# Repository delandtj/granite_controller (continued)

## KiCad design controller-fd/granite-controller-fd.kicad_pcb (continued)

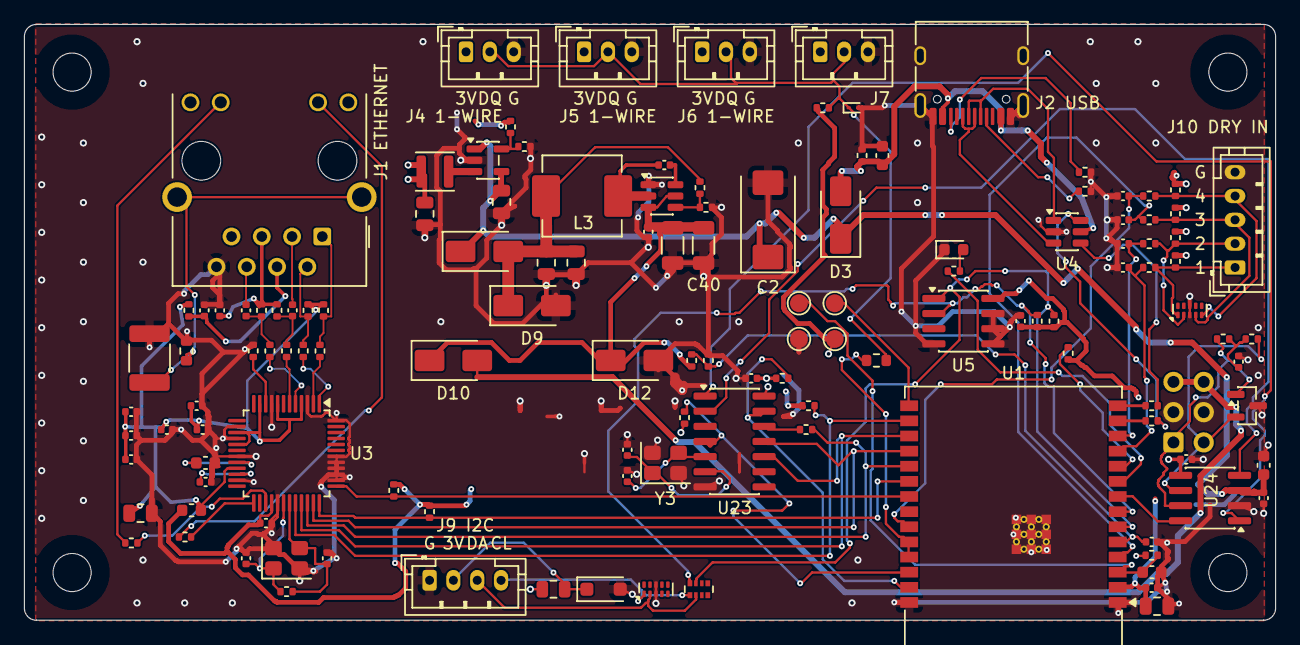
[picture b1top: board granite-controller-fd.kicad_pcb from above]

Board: 4 copper layers, 105.0 x 50.0 mm, 134 parts (1 on the bottom side), 81 nets.

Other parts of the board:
H1, H2, H3, H4: MountingHole_3.2mm_M3

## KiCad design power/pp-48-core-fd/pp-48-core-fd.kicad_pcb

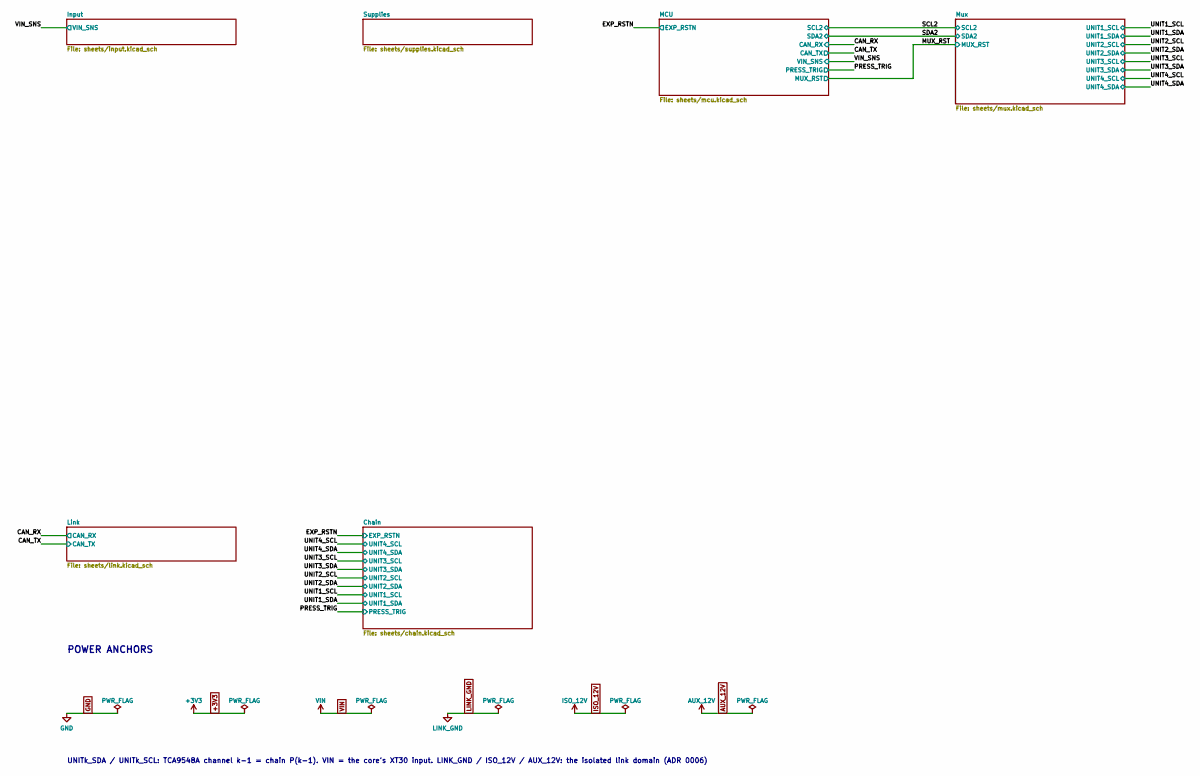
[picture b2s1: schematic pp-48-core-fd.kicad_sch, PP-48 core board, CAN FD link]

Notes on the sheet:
POWER ANCHORS
UNITk_SDA / UNITk_SCL: TCA9548A channel k-1 = chain P(k-1). VIN = the core's XT30 input. LINK_GND / ISO_12V / AUX_12V: the isolated link domain (ADR 0006)

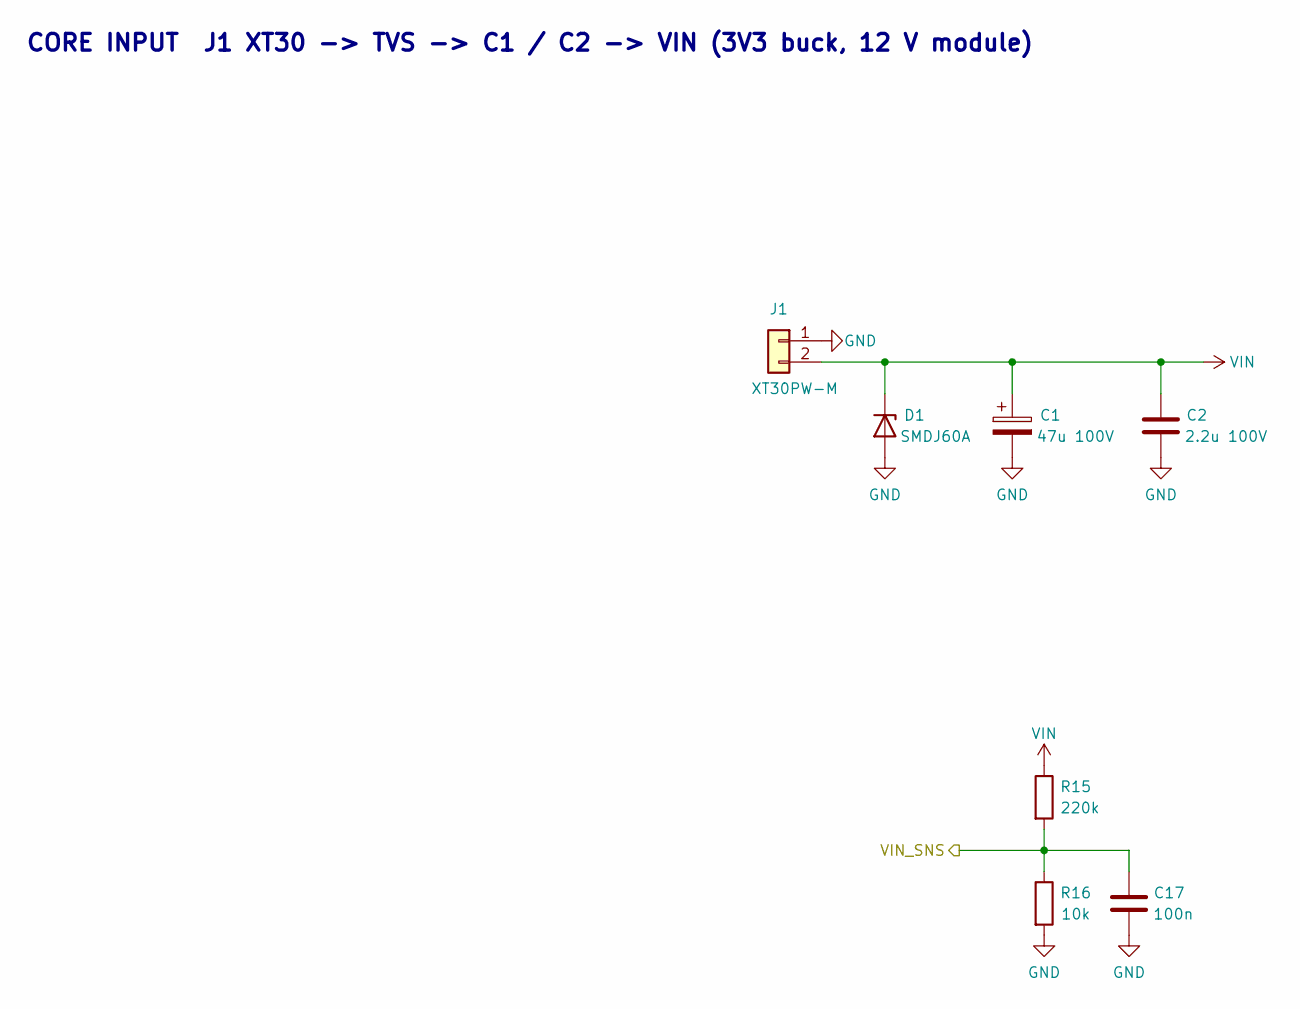
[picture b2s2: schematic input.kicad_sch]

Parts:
C1: 47u 100V; CP_Elec_10x10; MPN Lelon RVT2A470M1010; LCSC C87862
C2: 2.2u 100V; C_1210_3225Metric; LCSC C338133
C17: 100n; C_0402_1005Metric; LCSC C1525
D1: SMDJ60A; D_SMC; LCSC C2990209
J1: XT30PW-M; AMASS_XT30PW-M_1x02_P2.50mm_Horizontal; MPN Amass XT30PW-M; LCSC C431092
R15: 220k; R_0805_2012Metric; LCSC C17556
R16: 10k; R_0402_1005Metric; LCSC C25744

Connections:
/VIN_SNS: C17.1, R15.2, R16.1; also elsewhere on the board
GND: C1.2, C2.2, C17.2, D1.2 (A), J1.1, R16.2; also elsewhere on the board
VIN: C1.1, C2.1, D1.1 (K), J1.2, R15.1; also elsewhere on the board

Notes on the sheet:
CORE INPUT J1 XT30 -> TVS -> C1 / C2 -> VIN (3V3 buck, 12 V module)

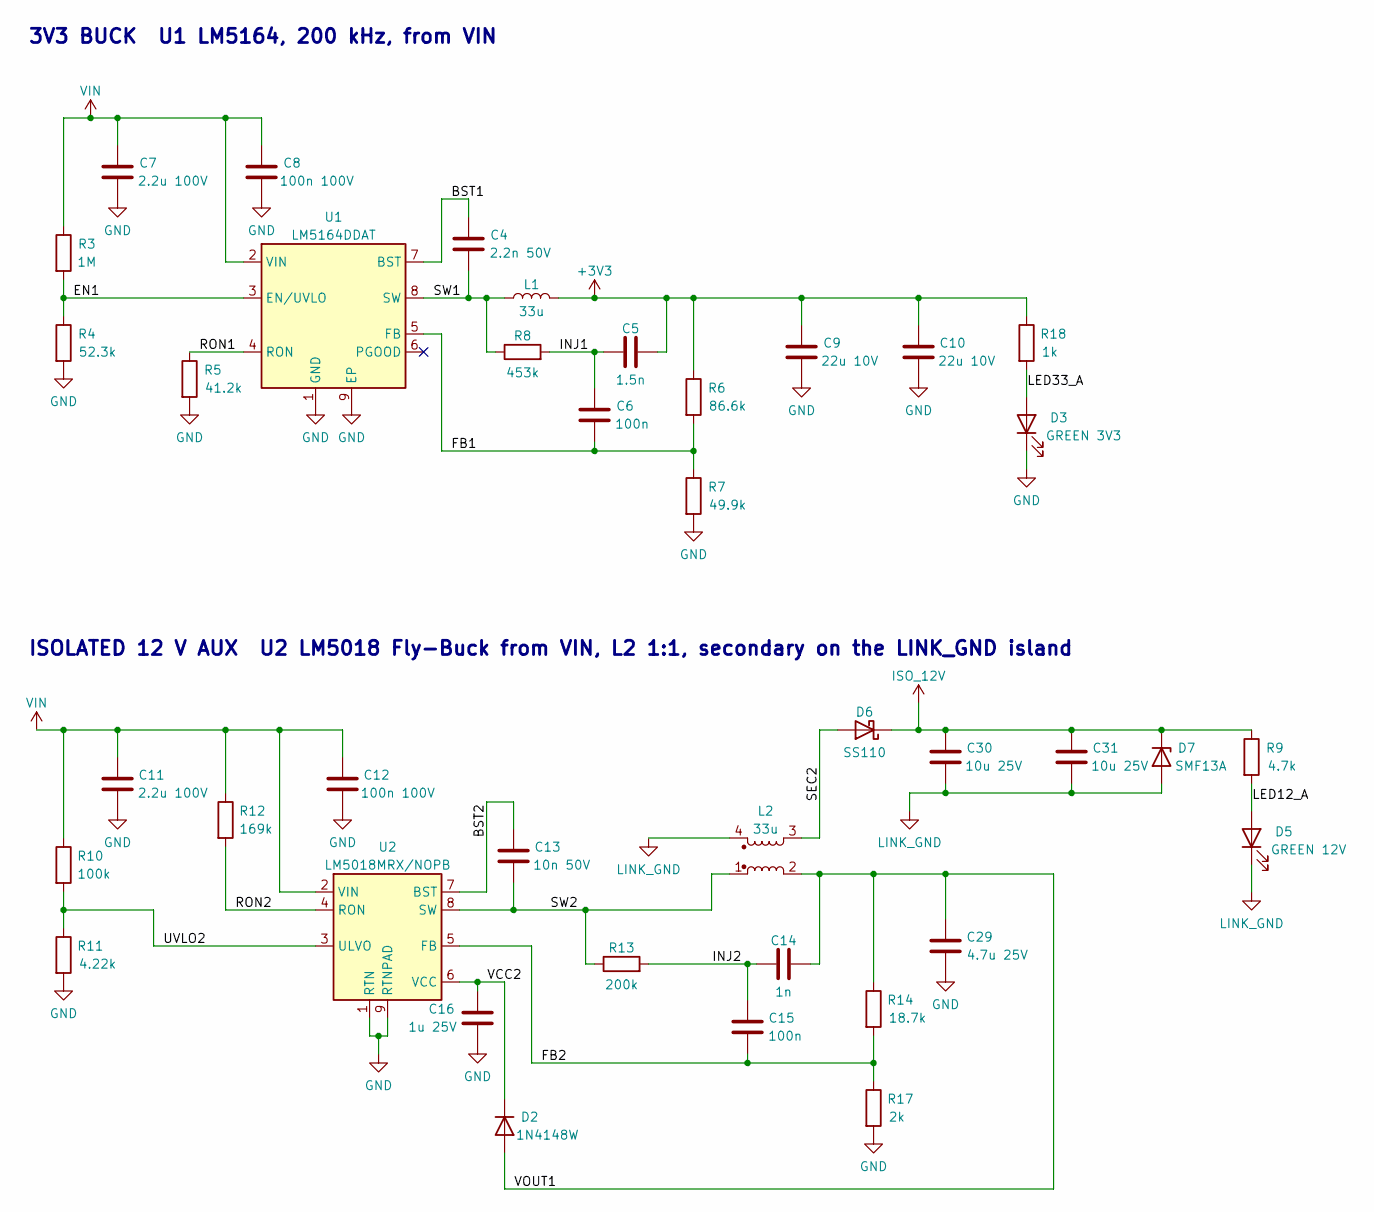
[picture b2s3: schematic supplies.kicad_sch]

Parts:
C4: 2.2n 50V; C_0402_1005Metric; LCSC C1531
C5: 1.5n; C_0402_1005Metric; LCSC C107022
C6, C15: 100n; C_0402_1005Metric; LCSC C1525
C7, C11: 2.2u 100V; C_1210_3225Metric; LCSC C338133
C8, C12: 100n 100V; C_0603_1608Metric; LCSC C696916
C9, C10: 22u 10V; C_1210_3225Metric; LCSC C318780
C13: 10n 50V; C_0402_1005Metric; LCSC C15195
C14: 1n; C_0402_1005Metric; LCSC C1523
C16: 1u 25V; C_0603_1608Metric; LCSC C15849
C29: 4.7u 25V; C_0805_2012Metric; LCSC C1779
C30, C31: 10u 25V; C_0805_2012Metric; LCSC C15850
D2: 1N4148W; D_SOD-123; LCSC C917030
D3: GREEN 3V3; LED_0603_1608Metric; LCSC C12624
D5: GREEN 12V; LED_0603_1608Metric; LCSC C12624
D6: SS110; D_SMA; LCSC C2482
D7: SMF13A; D_SOD-123F; LCSC C353315
L1: 33u; L_Bourns_SRR1260; MPN Bourns SRR1260-330M; LCSC C840528
L2: 33u; L_Coilcraft_LPD5030V; MPN Coilcraft LPD5030V-333MRC; LCSC C5441621
R3: 1M; R_0805_2012Metric; LCSC C17514
R4: 52.3k; R_0402_1005Metric; LCSC C2998086
R5: 41.2k; R_0402_1005Metric; LCSC C2998053
R6: 86.6k; R_0402_1005Metric; LCSC C48533697
R7: 49.9k; R_0402_1005Metric; LCSC C137969
R8: 453k; R_0402_1005Metric; LCSC C27009
R9: 4.7k; R_0603_1608Metric; LCSC C23162
R10: 100k; R_0805_2012Metric; LCSC C149504
R11: 4.22k; R_0402_1005Metric; LCSC C25898
R12: 169k; R_0805_2012Metric; LCSC C2933337
R13: 200k; R_0805_2012Metric; LCSC C17539
R14: 18.7k; R_0402_1005Metric; LCSC C5153953
R17: 2k; R_0402_1005Metric; LCSC C4109
R18: 1k; R_0402_1005Metric; LCSC C11702
U1: LM5164DDAT; HSOP-8-1EP_3.9x4.9mm_P1.27mm_EP2.41x3.1mm; LCSC C2071198
U2: LM5018MRX/NOPB; SOIC-8-1EP_3.9x4.9mm_P1.27mm_EP2.95x4.9mm_Mask2.71x3.4mm_Th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; LCSC C471040

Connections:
+3V3: C5.2, C9.1, C10.1, L1.2, R6.1, R18.1; also elsewhere on the board
/Supplies/BST1: C4.1, U1.7 (BST)
/Supplies/BST2: C13.1, U2.7 (BST)
/Supplies/EN1: R3.2, R4.1, U1.3 (EN/UVLO)
/Supplies/FB1: C6.2, R6.2, R7.1, U1.5 (FB)
/Supplies/FB2: C15.2, R14.2, R17.1, U2.5 (FB)
/Supplies/INJ1: C5.1, C6.1, R8.2
/Supplies/INJ2: C14.1, C15.1, R13.2
/Supplies/LED12_A: D5.2 (A), R9.2
/Supplies/LED33_A: D3.2 (A), R18.2
/Supplies/RON1: R5.1, U1.4 (RON)
/Supplies/RON2: R12.2, U2.4 (RON)
/Supplies/SEC2: D6.2 (A), L2.3
/Supplies/SW1: C4.2, L1.1, R8.1, U1.8 (SW)
/Supplies/SW2: C13.2, L2.1, R13.1, U2.8 (SW)
/Supplies/UVLO2: R10.2, R11.1, U2.3 (ULVO)
/Supplies/VCC2: C16.1, D2.1 (K), U2.6 (VCC)
/Supplies/VOUT1: C14.2, C29.1, D2.2 (A), L2.2, R14.1
GND: C7.2, C8.2, C9.2, C10.2, C11.2, C12.2, C16.2, C29.2, D3.1 (K), R4.2, R5.2, R7.2, R11.2, R17.2, U1.1 (GND), U1.9 (EP), U2.1 (RTN), U2.9 (RTNPAD); also elsewhere on the board
ISO_12V: C30.1, C31.1, D6.1 (K), D7.1 (K), R9.1; also elsewhere on the board
LINK_GND: C30.2, C31.2, D5.1 (K), D7.2 (A), L2.4; also elsewhere on the board
VIN: C7.1, C8.1, C11.1, C12.1, R3.1, R10.1, R12.1, U1.2 (VIN), U2.2 (VIN); also elsewhere on the board

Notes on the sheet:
3V3 BUCK U1 LM5164, 200 kHz, from VIN
ISOLATED 12 V AUX U2 LM5018 Fly-Buck from VIN, L2 1:1, secondary on the LINK_GND island

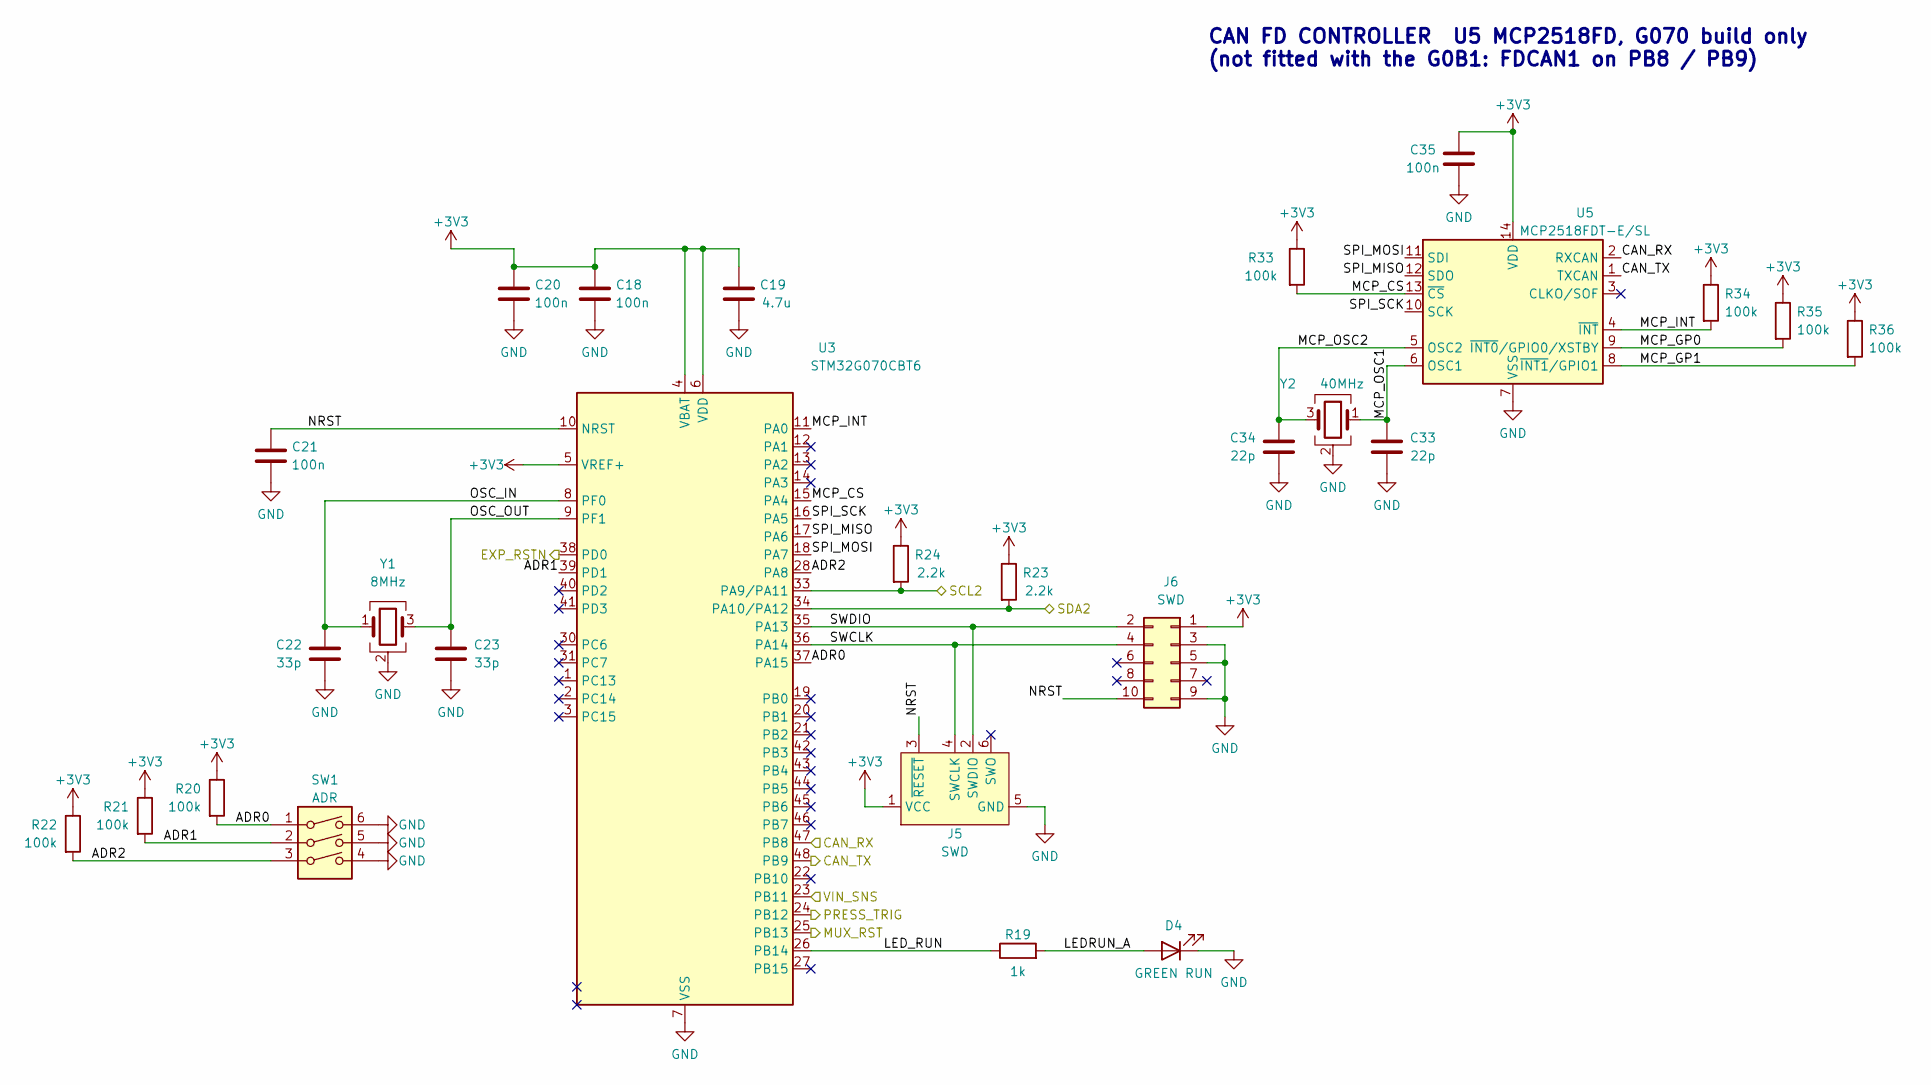
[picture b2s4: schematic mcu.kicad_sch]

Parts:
C18, C20, C21: 100n; C_0402_1005Metric; LCSC C1525
C19: 4.7u; C_0603_1608Metric; LCSC C19666
C22, C23: 33p; C_0402_1005Metric; LCSC C1562
C33, C34: 22p; C_0402_1005Metric; MPN FH 0402CG220J500NT; LCSC C1555
C35: 100n; C_0402_1005Metric; MPN Samsung CL05B104KO5NNNC; LCSC C1525
D4: GREEN RUN; LED_0603_1608Metric; LCSC C12624
J5: SWD; Tag-Connect_TC2030-IDC-NL_2x03_P1.27mm_Vertical
J6: SWD; PinHeader_2x05_P1.27mm_Vertical_SMD; MPN Samtec FTSH-105-01-L-DV-K; LCSC C5155080
R19: 1k; R_0402_1005Metric; LCSC C11702
R20, R21, R22: 100k; R_0402_1005Metric; LCSC C25741
R23, R24: 2.2k; R_0402_1005Metric; LCSC C25879
R33, R34, R35, R36: 100k; R_0402_1005Metric; MPN UniOhm 0402WGF1003TCE; LCSC C25741
SW1: ADR; SW_DIP_SPSTx03_Slide_KingTek_DSHP03TS_W7.62mm_P1.27mm; MPN KingTek DSHP03TSGET; LCSC C50844
U3: STM32G070CBT6; LQFP-48_7x7mm_P0.5mm; LCSC C529338
U5: MCP2518FDT-E/SL; SOIC-14_3.9x8.7mm_P1.27mm; MPN Microchip MCP2518FDT-E/SL; LCSC C626758
Y1: 8MHz; Crystal_SMD_3225-4Pin_3.2x2.5mm; LCSC C7424755
Y2: 40MHz; Crystal_SMD_3225-4Pin_3.2x2.5mm; MPN YXC X322540MPB4SI; LCSC C9010

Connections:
+3V3: C18.1, C19.1, C20.1, C35.1, J5.1 (VCC), J6.1, R20.1, R21.1, R22.1, R23.1, R24.1, R33.1, R34.1, R35.1, R36.1, U3.4 (VBAT), U3.5 (VREF+), U3.6 (VDD), U5.14 (VDD); also elsewhere on the board
/CAN_RX: U3.47 (PB8), U5.2 (RXCAN); also elsewhere on the board
/CAN_TX: U3.48 (PB9), U5.1 (TXCAN); also elsewhere on the board
/EXP_RSTN: U3.38 (PD0); also elsewhere on the board
/MCU/ADR0: R20.2, SW1.1, U3.37 (PA15)
/MCU/ADR1: R21.2, SW1.2, U3.39 (PD1)
/MCU/ADR2: R22.2, SW1.3, U3.28 (PA8)
/MCU/LEDRUN_A: D4.2 (A), R19.2
/MCU/LED_RUN: R19.1, U3.26 (PB14)
/MCU/MCP_CS: R33.2, U3.15 (PA4), U5.13 (~CS)
/MCU/MCP_GP0: R35.2, U5.9 (~INT0/GPIO0/XSTBY)
/MCU/MCP_GP1: R36.2, U5.8 (~INT1/GPIO1)
/MCU/MCP_INT: R34.2, U3.11 (PA0), U5.4 (~INT)
/MCU/MCP_OSC1: C33.1, U5.6 (OSC1), Y2.1
/MCU/MCP_OSC2: C34.1, U5.5 (OSC2), Y2.3
/MCU/NRST: C21.1, J5.3 (~RESET), J6.10, U3.10 (NRST)
/MCU/OSC_IN: C22.1, U3.8 (PF0), Y1.1
/MCU/OSC_OUT: C23.1, U3.9 (PF1), Y1.3
/MCU/SPI_MISO: U3.17 (PA6), U5.12 (SDO)
/MCU/SPI_MOSI: U3.18 (PA7), U5.11 (SDI)
/MCU/SPI_SCK: U3.16 (PA5), U5.10 (SCK)
/MCU/SWCLK: J5.4 (SWCLK), J6.4, U3.36 (PA14)
/MCU/SWDIO: J5.2 (SWDIO), J6.2, U3.35 (PA13)
/MUX_RST: U3.25 (PB13); also elsewhere on the board
/PRESS_TRIG: U3.24 (PB12); also elsewhere on the board
/SCL2: R24.2, U3.33 (PA9/PA11); also elsewhere on the board
/SDA2: R23.2, U3.34 (PA10/PA12); also elsewhere on the board
/VIN_SNS: U3.23 (PB11); also elsewhere on the board
GND: C18.2, C19.2, C20.2, C21.2, C22.2, C23.2, C33.2, C34.2, C35.2, D4.1 (K), J5.5 (GND), J6.3, J6.5, J6.9, SW1.4, SW1.5, SW1.6, U3.7 (VSS), U5.7 (VSS), Y1.2 (G), Y1.4 (G), Y2.2 (G), Y2.4 (G); also elsewhere on the board

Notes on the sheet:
CAN FD CONTROLLER U5 MCP2518FD, G070 build only (not fitted with the G0B1: FDCAN1 on PB8 / PB9)

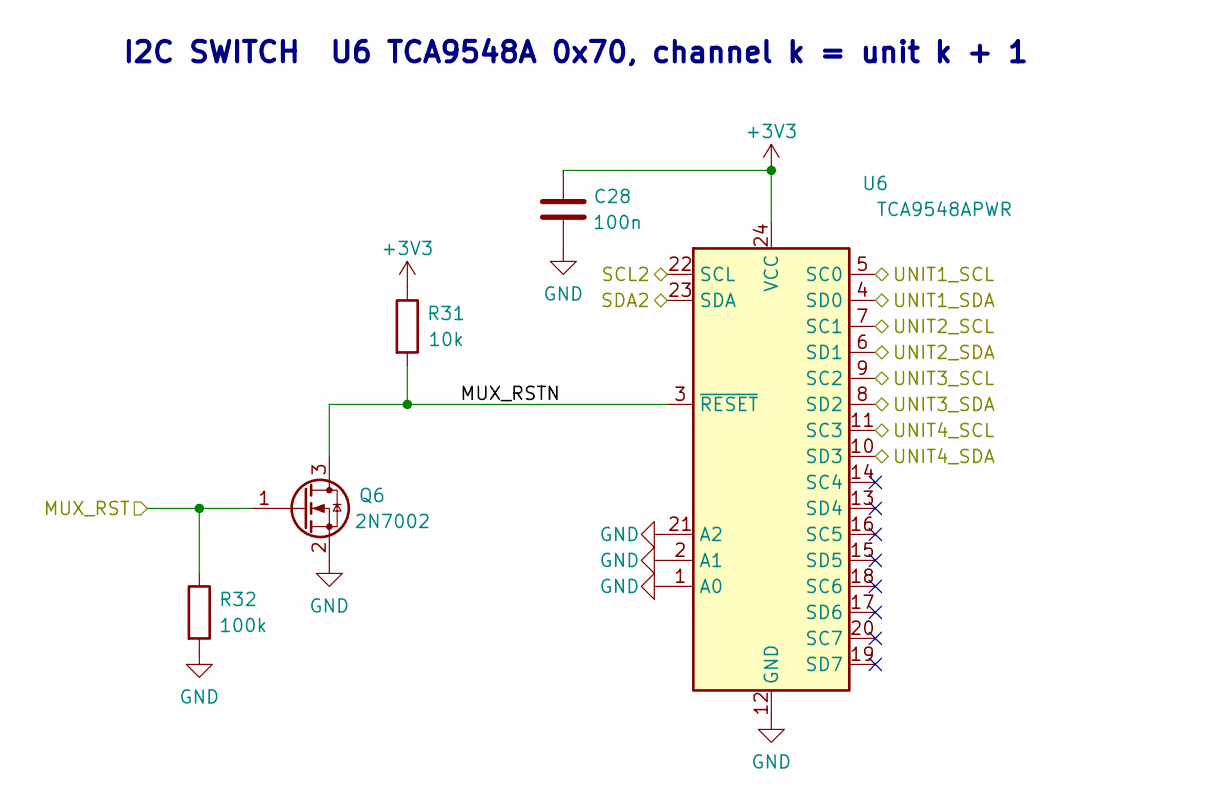
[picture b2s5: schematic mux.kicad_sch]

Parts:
C28: 100n; C_0402_1005Metric; LCSC C1525
Q6: 2N7002; SOT-23; LCSC C8545
R31: 10k; R_0402_1005Metric; LCSC C25744
R32: 100k; R_0402_1005Metric; LCSC C25741
U6: TCA9548APWR; TSSOP-24_4.4x7.8mm_P0.65mm; LCSC C130026

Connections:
+3V3: C28.1, R31.1, U6.24 (VCC); also elsewhere on the board
/MUX_RST: Q6.1 (G), R32.1; also elsewhere on the board
/Mux/MUX_RSTN: Q6.3 (D), R31.2, U6.3 (~RESET)
/SCL2: U6.22 (SCL); also elsewhere on the board
/SDA2: U6.23 (SDA); also elsewhere on the board
/UNIT1_SCL: U6.5 (SC0); also elsewhere on the board
/UNIT1_SDA: U6.4 (SD0); also elsewhere on the board
/UNIT2_SCL: U6.7 (SC1); also elsewhere on the board
/UNIT2_SDA: U6.6 (SD1); also elsewhere on the board
/UNIT3_SCL: U6.9 (SC2); also elsewhere on the board
/UNIT3_SDA: U6.8 (SD2); also elsewhere on the board
/UNIT4_SCL: U6.11 (SC3); also elsewhere on the board
/UNIT4_SDA: U6.10 (SD3); also elsewhere on the board
GND: C28.2, Q6.2 (S), R32.2, U6.1 (A0), U6.2 (A1), U6.12 (GND), U6.21 (A2); also elsewhere on the board

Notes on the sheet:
I2C SWITCH U6 TCA9548A 0x70, channel k = unit k + 1

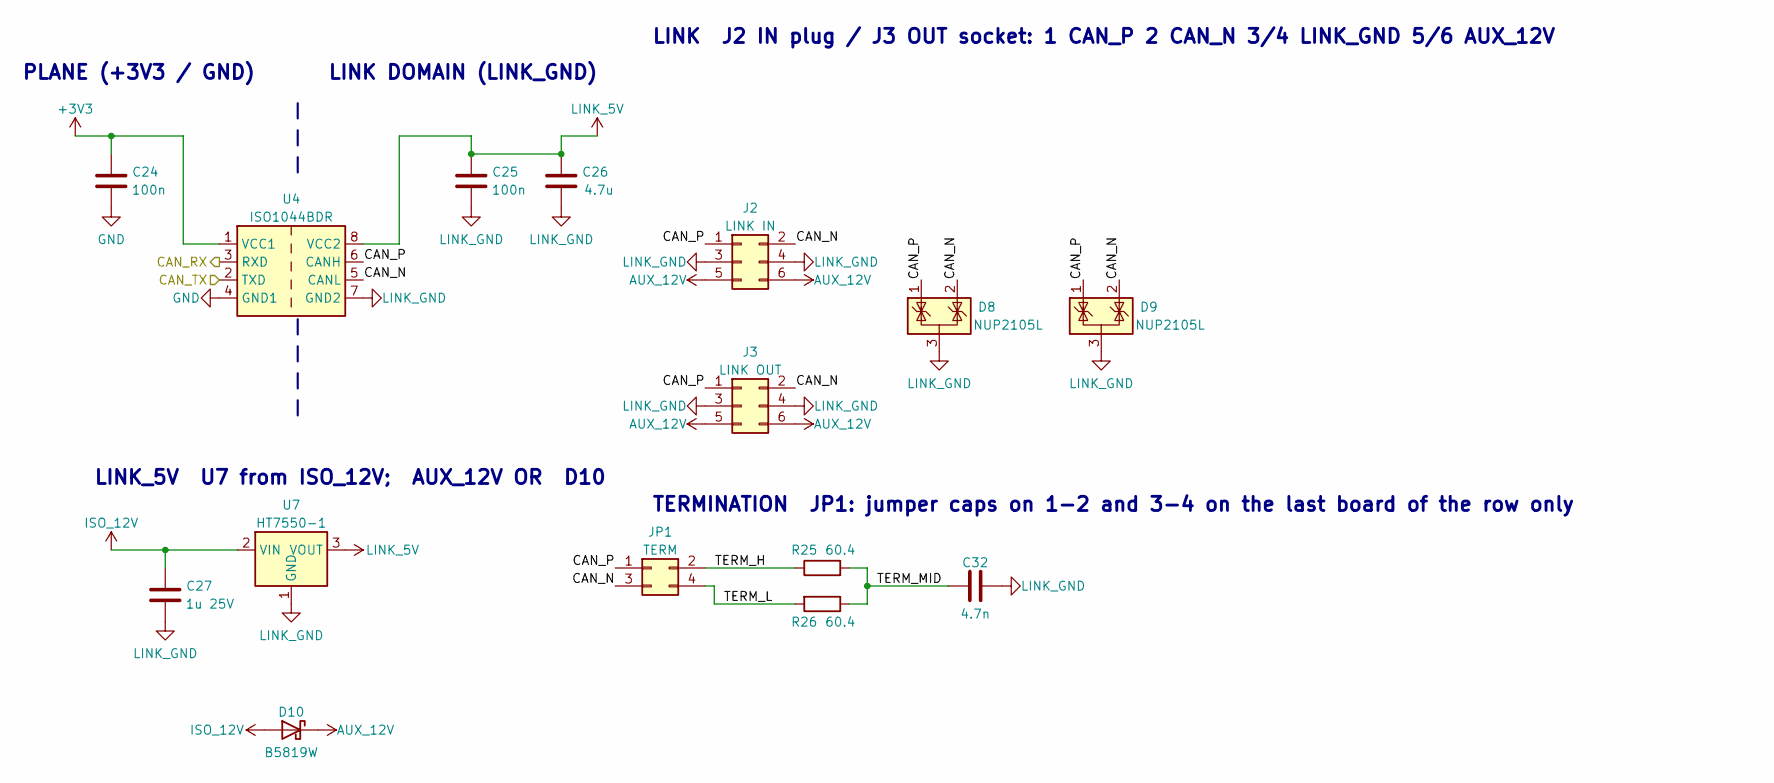
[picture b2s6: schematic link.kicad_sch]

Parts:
C24, C25: 100n; C_0402_1005Metric; MPN Samsung CL05B104KO5NNNC; LCSC C1525
C26: 4.7u; C_0603_1608Metric; MPN Samsung CL10A475KO8NNNC; LCSC C19666
C27: 1u 25V; C_0603_1608Metric; MPN Samsung CL10A105KB8NNNC; LCSC C15849
C32: 4.7n; C_0402_1005Metric; MPN FH 0402B472K500NT; LCSC C1538
D8, D9: NUP2105L; SOT-23; MPN onsemi NUP2105LT1G; LCSC C14486
D10: B5819W; D_SOD-123; MPN SL B5819W; LCSC C8598
J2: LINK IN; PinHeader_2x03_P2.54mm_Horizontal; MPN CJT A2541WR-2x3P; LCSC C239334
J3: LINK OUT; PinSocket_2x03_P2.54mm_Horizontal; MPN CJT A2541HWR-2x3P; LCSC C5333425
JP1: TERM; PinHeader_2x02_P2.54mm_Vertical; MPN XFCN PZ254V-12-4P; LCSC C492419
R25, R26: 60.4; R_0603_1608Metric; MPN Yageo RC0603FR-0760R4L; LCSC C245987
U4: ISO1044BDR; SOIC-8_3.9x4.9mm_P1.27mm; MPN TI ISO1044BDR; LCSC C2878225
U7: HT7550-1; SOT-89-3; MPN Holtek HT7550-1; LCSC C16106

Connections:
+3V3: C24.1, U4.1 (VCC1); also elsewhere on the board
/CAN_RX: U4.3 (RXD); also elsewhere on the board
/CAN_TX: U4.2 (TXD); also elsewhere on the board
/Link/CAN_N: D8.2 (K), D9.2 (K), J2.2, J3.2, JP1.3, U4.5 (CANL)
/Link/CAN_P: D8.1 (K), D9.1 (K), J2.1, J3.1, JP1.1, U4.6 (CANH)
/Link/TERM_H: JP1.2, R25.1
/Link/TERM_L: JP1.4, R26.2
/Link/TERM_MID: C32.1, R25.2, R26.1
AUX_12V: D10.1 (K), J2.5, J2.6, J3.5, J3.6
GND: C24.2, U4.4 (GND1); also elsewhere on the board
ISO_12V: C27.1, D10.2 (A), U7.2 (VIN); also elsewhere on the board
LINK_5V: C25.1, C26.1, U4.8 (VCC2), U7.3 (VOUT)
LINK_GND: C25.2, C26.2, C27.2, C32.2, D8.3 (A), D9.3 (A), J2.3, J2.4, J3.3, J3.4, U4.7 (GND2), U7.1 (GND); also elsewhere on the board

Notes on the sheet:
LINK_5V U7 from ISO_12V; AUX_12V OR D10
PLANE (+3V3 / GND)
LINK DOMAIN (LINK_GND)
LINK J2 IN plug / J3 OUT socket: 1 CAN_P 2 CAN_N 3/4 LINK_GND 5/6 AUX_12V
TERMINATION JP1: jumper caps on 1-2 and 3-4 on the last board of the row only

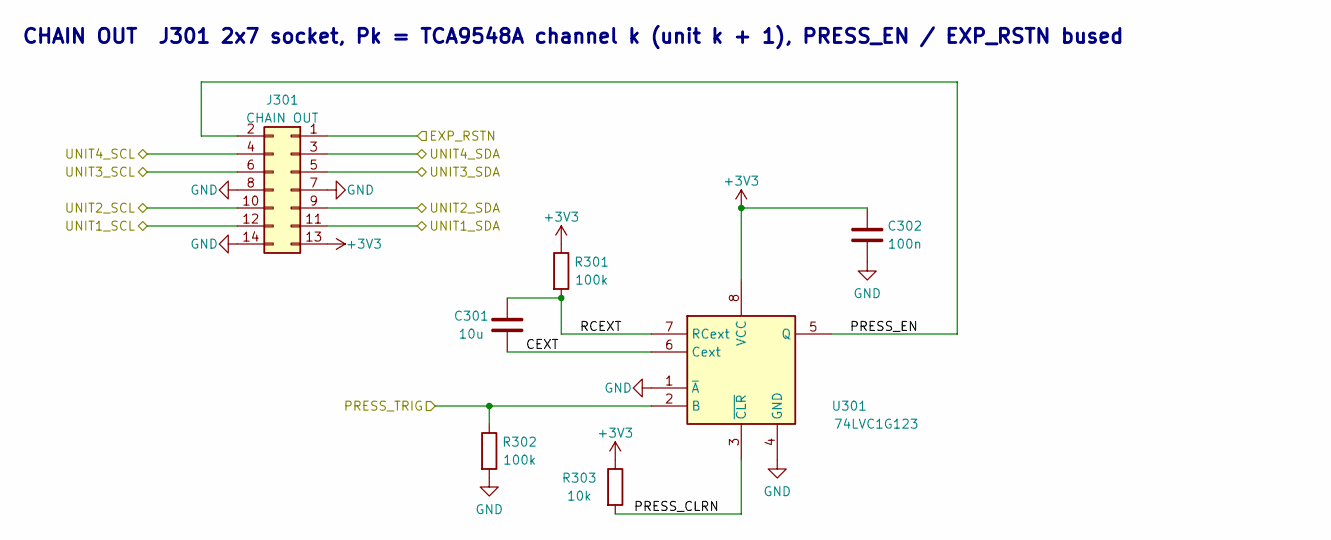
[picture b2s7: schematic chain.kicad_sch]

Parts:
C301: 10u; C_0805_2012Metric; LCSC C15850
C302: 100n; C_0402_1005Metric; LCSC C1525
J301: CHAIN OUT; PinSocket_2x07_P2.54mm_Horizontal; MPN CJT A2541HWR-2x7P; LCSC C19100281
R301, R302: 100k; R_0402_1005Metric; LCSC C25741
R303: 10k; R_0402_1005Metric; LCSC C25744
U301: 74LVC1G123; SSOP-8_2.95x2.8mm_P0.65mm; MPN TI SN74LVC1G123DCTR; LCSC C123302

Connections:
+3V3: C302.1, J301.13, R301.1, R303.1, U301.8 (VCC); also elsewhere on the board
/Chain/CEXT: C301.2, U301.6 (Cext)
/Chain/PRESS_CLRN: R303.2, U301.3 (~CLR)
/Chain/PRESS_EN: J301.2, U301.5 (Q)
/Chain/RCEXT: C301.1, R301.2, U301.7 (RCext)
/EXP_RSTN: J301.1; also elsewhere on the board
/PRESS_TRIG: R302.1, U301.2 (B); also elsewhere on the board
/UNIT1_SCL: J301.12; also elsewhere on the board
/UNIT1_SDA: J301.11; also elsewhere on the board
/UNIT2_SCL: J301.10; also elsewhere on the board
/UNIT2_SDA: J301.9; also elsewhere on the board
/UNIT3_SCL: J301.6; also elsewhere on the board
/UNIT3_SDA: J301.5; also elsewhere on the board
/UNIT4_SCL: J301.4; also elsewhere on the board
/UNIT4_SDA: J301.3; also elsewhere on the board
GND: C302.2, J301.7, J301.8, J301.14, R302.2, U301.1 (~A), U301.4 (GND); also elsewhere on the board

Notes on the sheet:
CHAIN OUT J301 2x7 socket, Pk = TCA9548A channel k (unit k + 1), PRESS_EN / EXP_RSTN bused

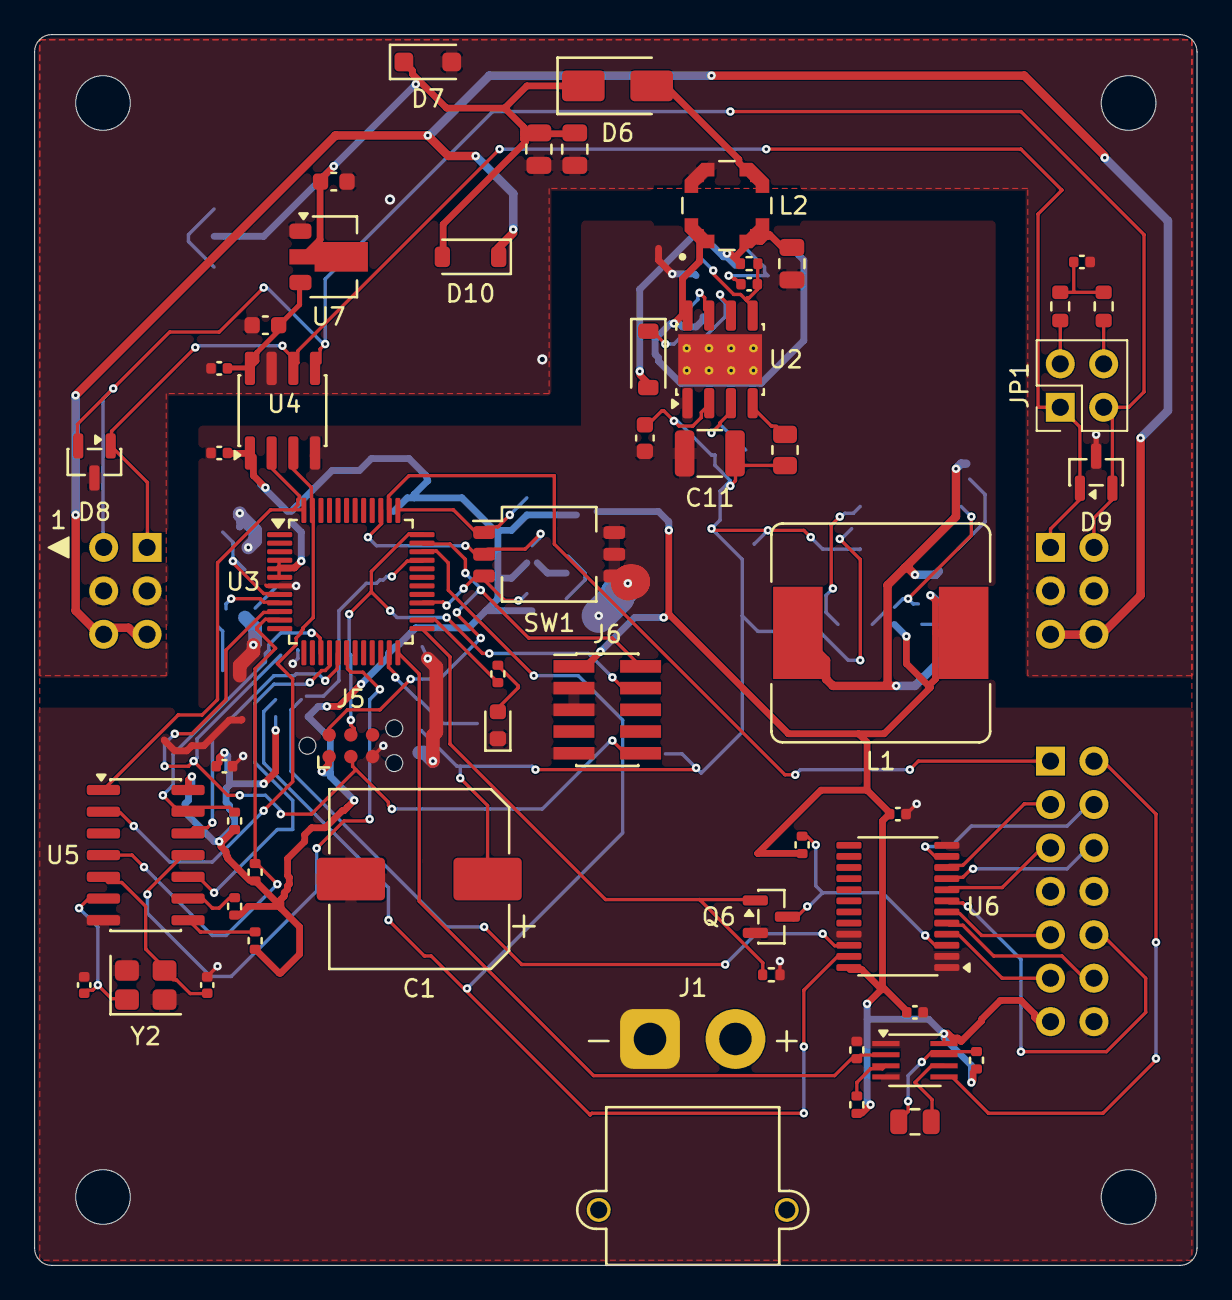
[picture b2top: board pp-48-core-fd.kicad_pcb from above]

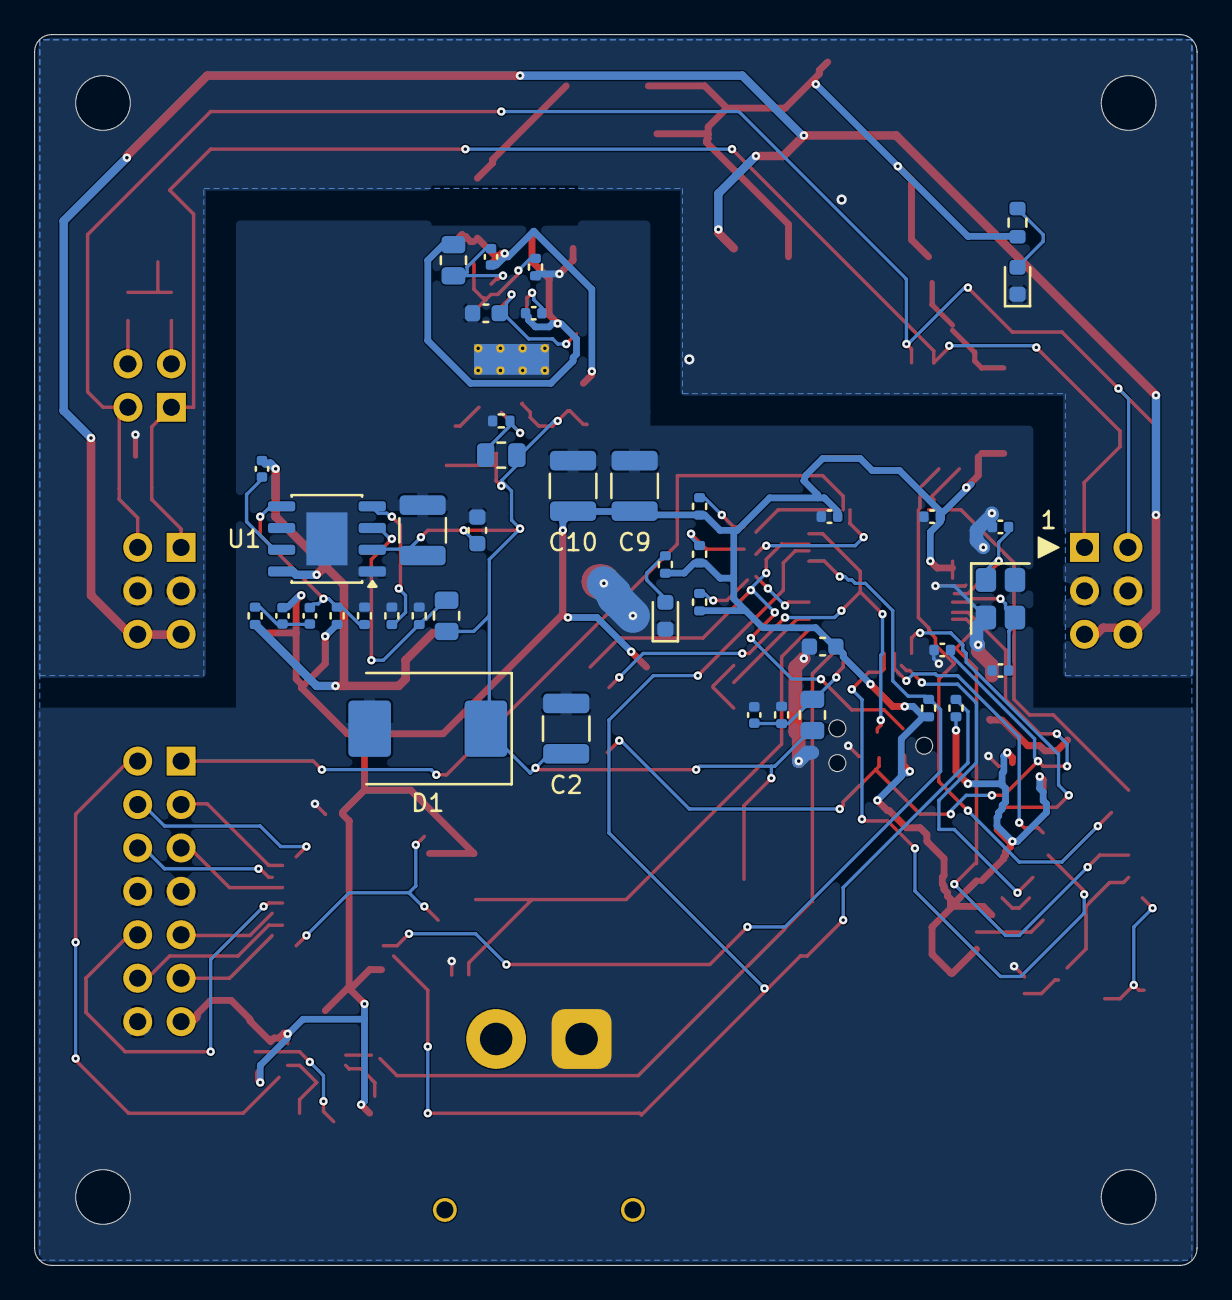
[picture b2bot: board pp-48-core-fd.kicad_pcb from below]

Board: 4 copper layers, 68.0 x 72.0 mm, 104 parts (45 on the bottom side), 69 nets.

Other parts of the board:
H1, H2, H3, H4: MountingHole_3.2mm_M3
